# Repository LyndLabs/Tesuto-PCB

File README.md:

# Tesuto: Minimal 16-Key Calculator using ESP32
A project I designed for my roomate's birthday, maybe someday I'll make it into something useful.

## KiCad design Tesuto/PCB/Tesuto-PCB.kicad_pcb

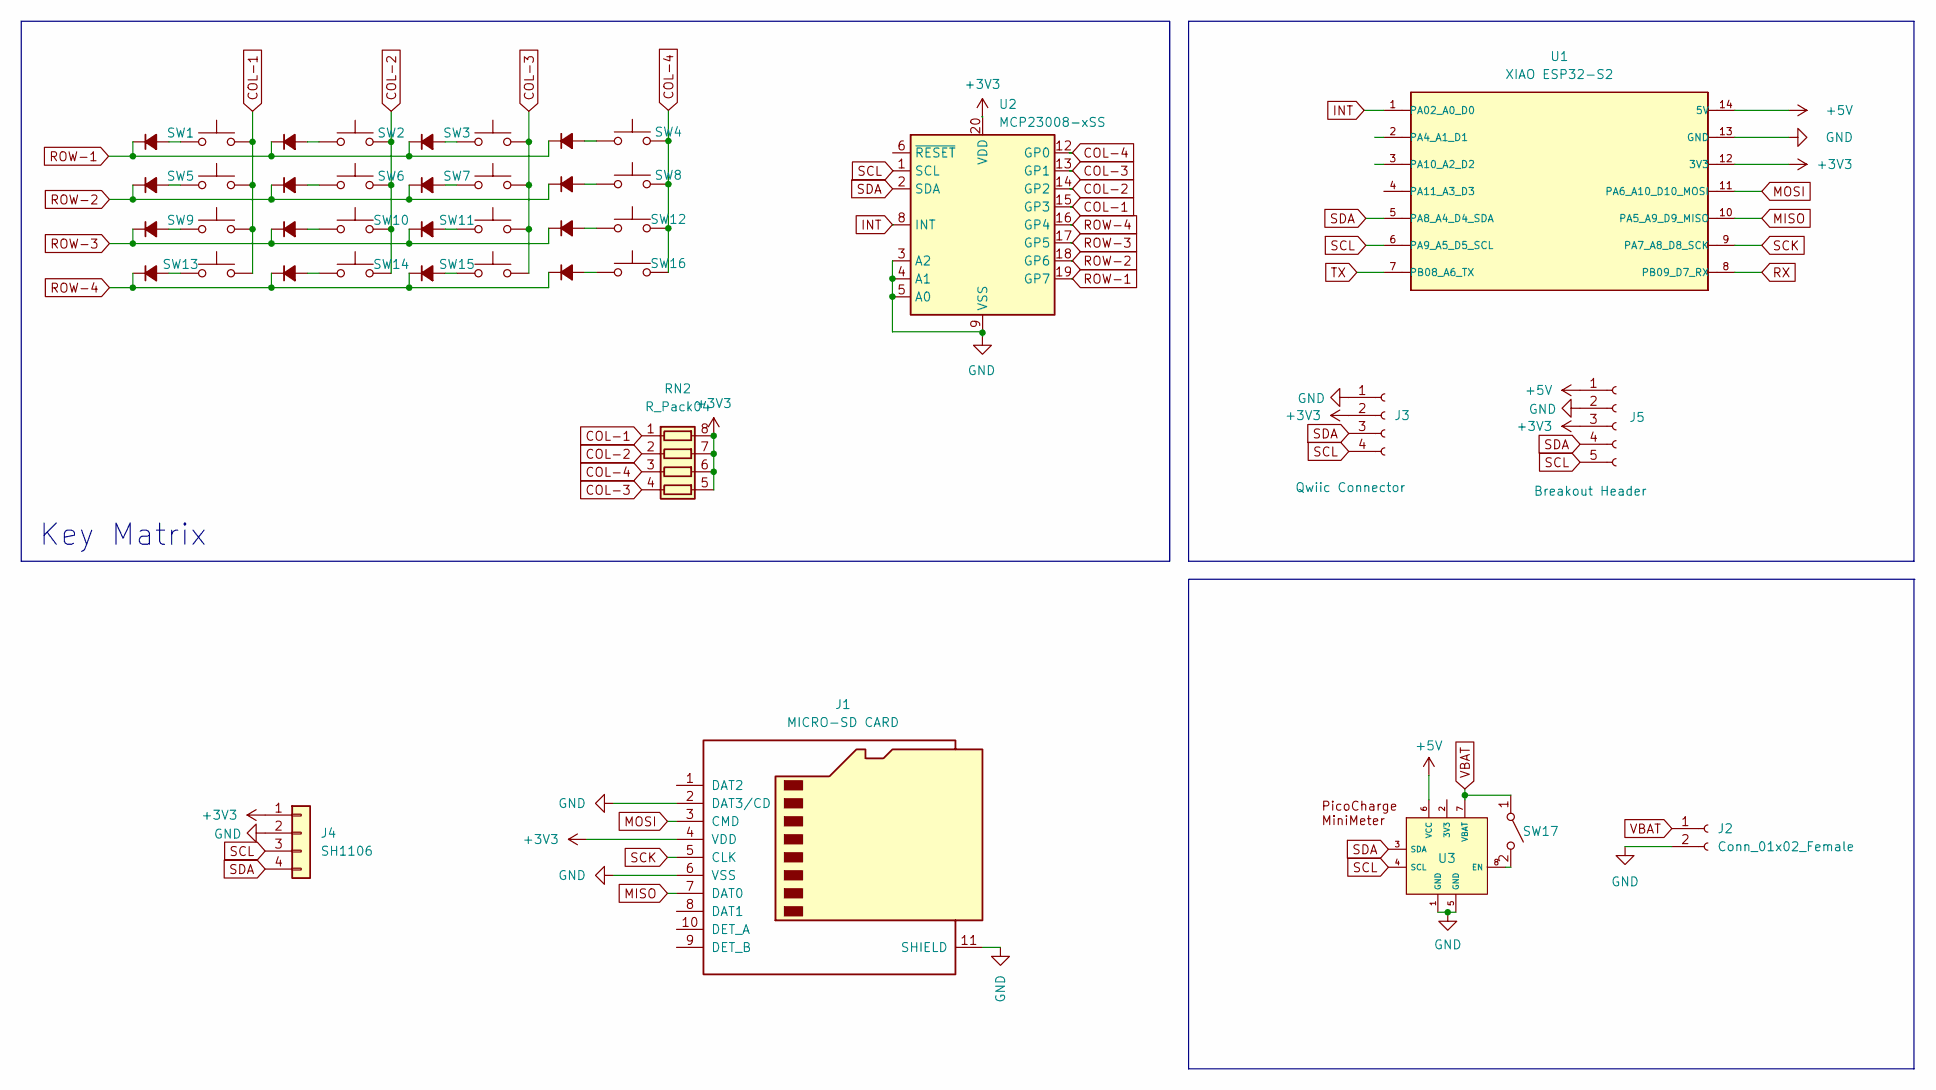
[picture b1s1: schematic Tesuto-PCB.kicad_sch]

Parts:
D1, D2, D3, D4, D5, D6, D7, D8, D9, D10, D11, D12, D13, D14, D15, D16: D_Small_Filled
J1: MICRO-SD CARD; MicroSD
J2: Conn_01x02_Female; JST_PH_S2B-PH-SM4-TB_1x02-1MP_P2.00mm_Horizontal
J3: Qwiic Connector; JST_SH_SM04B-SRSS-TB_1x04-1MP_P1.00mm_Horizontal
J4: SH1106; PinHeader_1x04_P2.54mm_Vertical
J5: Breakout Header; PinHeader_1x05_P2.54mm_Vertical_SMD_Pin1Left
RN2: R_Pack04; R_Array_Convex_4x1206
SW1, SW2, SW3, SW4, SW5, SW6, SW7, SW8, SW9, SW10, SW11, SW12, SW13, SW14, SW15, SW16: Up
SW17: SW_SPST
U1: XIAO ESP32-S2; MOUDLE14P-SMD-2.54-21X17.8MM
U2: MCP23008-xSS; SSOP-20_5.3x7.2mm_P0.65mm
U3: MiniMeter

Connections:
+3V3: J1.4 (VDD), J3.2, J4.1, RN2.5 (R4.2), RN2.6 (R3.2), RN2.7 (R2.2), RN2.8 (R1.2), U1.12 (3V3), U2.20 (VDD)
+5V: J5.1, U1.14 (5V), U3.6 (VCC)
COL-1: RN2.1 (R1.1), SW1.2, SW5.2, SW9.2, SW13.2, U2.15 (GP3)
COL-2: RN2.2 (R2.1), SW2.1, SW6.1, SW10.1, SW14.1, U2.14 (GP2)
COL-3: RN2.4 (R4.1), SW3.2, SW7.2, SW11.2, SW15.2, U2.13 (GP1)
COL-4: RN2.3 (R3.1), SW4.1, SW8.1, SW12.1, SW16.1, U2.12 (GP0)
GND: J1.2 (DAT3/CD), J1.6 (VSS), J1.11 (SHIELD), J2.2, J3.1, J4.2, J4.6, J4.11, J5.2, U1.13 (GND), U2.3 (A2), U2.4 (A1), U2.5 (A0), U2.9 (VSS), U3.1 (GND), U3.5 (GND)
INT: U1.1 (PA02_A0_D0), U2.8 (INT)
MISO: J1.7 (DAT0), U1.10 (PA5_A9_D9_MISO)
MOSI: J1.3 (CMD), U1.11 (PA6_A10_D10_MOSI)
unnamed: D1.2 (A), SW1.1
unnamed: D2.2 (A), SW5.1
unnamed: D3.2 (A), SW9.1
unnamed: D4.2 (A), SW13.1
unnamed: D5.2 (A), SW2.2
unnamed: D6.2 (A), SW6.2
unnamed: D7.2 (A), SW10.2
unnamed: D8.2 (A), SW14.2
unnamed: D9.2 (A), SW3.1
unnamed: D10.2 (A), SW7.1
unnamed: D11.2 (A), SW11.1
unnamed: D12.2 (A), SW15.1
unnamed: D13.2 (A), SW4.2
unnamed: D14.2 (A), SW8.2
unnamed: D15.2 (A), SW12.2
unnamed: D16.2 (A), SW16.2
unnamed: SW17.2 (B), U3.8 (EN)
ROW-1: D1.1 (K), D5.1 (K), D9.1 (K), D13.1 (K), U2.19 (GP7)
ROW-2: D2.1 (K), D6.1 (K), D10.1 (K), D14.1 (K), U2.18 (GP6)
ROW-3: D3.1 (K), D7.1 (K), D11.1 (K), D15.1 (K), U2.17 (GP5)
ROW-4: D4.1 (K), D8.1 (K), D12.1 (K), D16.1 (K), U2.16 (GP4)
RX: U1.8 (PB09_D7_RX)
SCK: J1.5 (CLK), U1.9 (PA7_A8_D8_SCK)
SCL: J2.3, J3.4, J4.3, J5.5, U1.6 (PA9_A5_D5_SCL), U2.1 (SCL), U3.4 (SCL)
SDA: J2.4, J3.3, J4.4, J5.4, U1.5 (PA8_A4_D4_SDA), U2.2 (SDA), U3.3 (SDA)
TX: U1.7 (PB08_A6_TX)
VBAT: J2.1, SW17.1 (A), U3.7 (VBAT)

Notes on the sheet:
Key Matrix

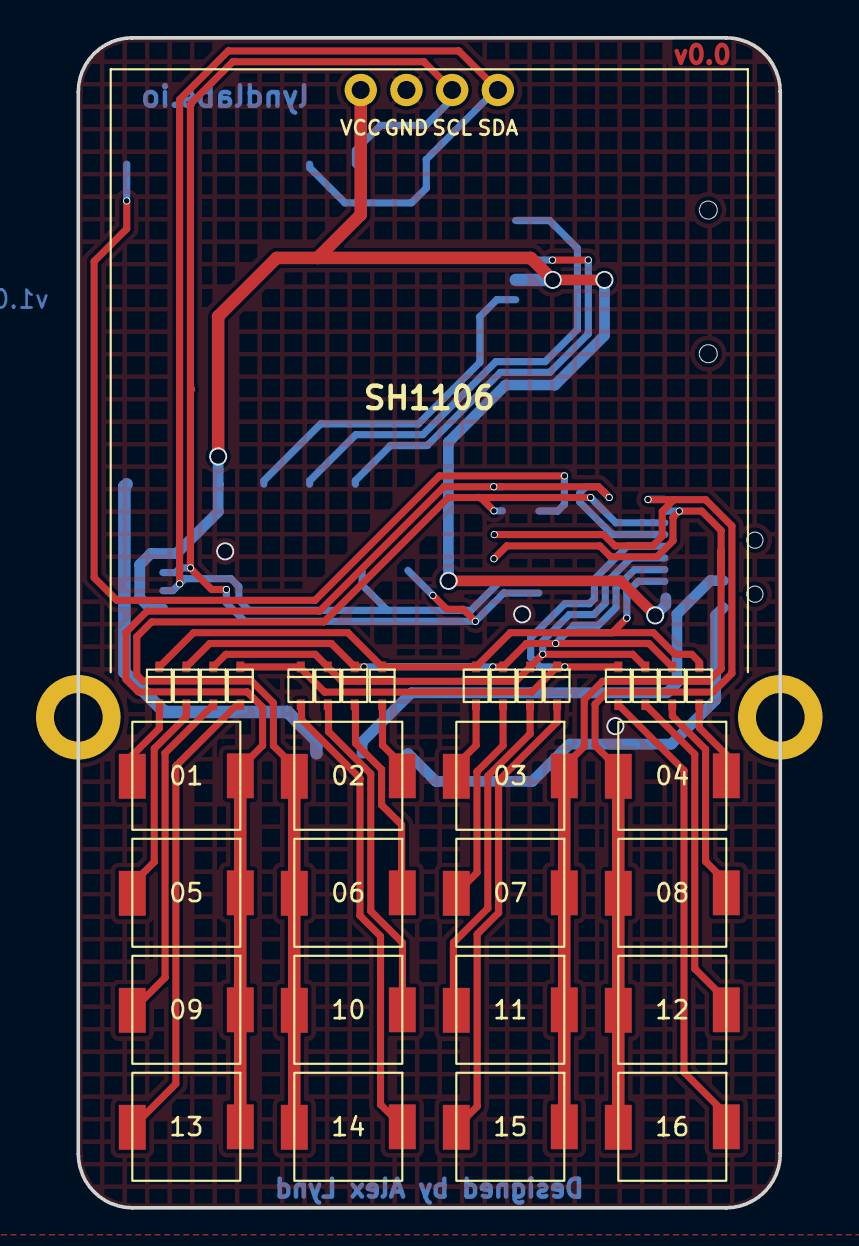
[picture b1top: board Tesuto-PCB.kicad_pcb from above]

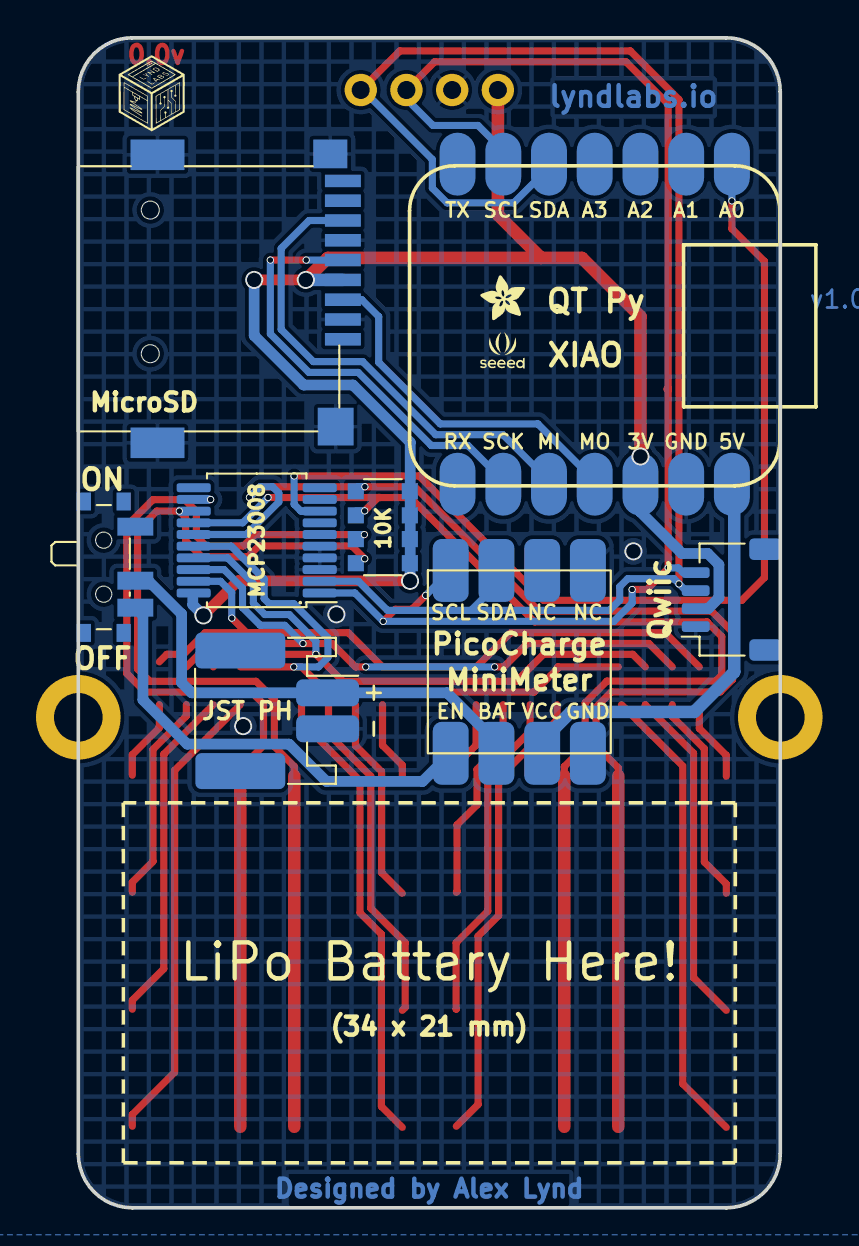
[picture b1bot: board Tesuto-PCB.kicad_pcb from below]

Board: 2 copper layers, 39.0 x 65.0 mm, 41 parts (8 on the bottom side), 35 nets.

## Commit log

2024-01-18 add v0.0 files
2024-01-18 add images
